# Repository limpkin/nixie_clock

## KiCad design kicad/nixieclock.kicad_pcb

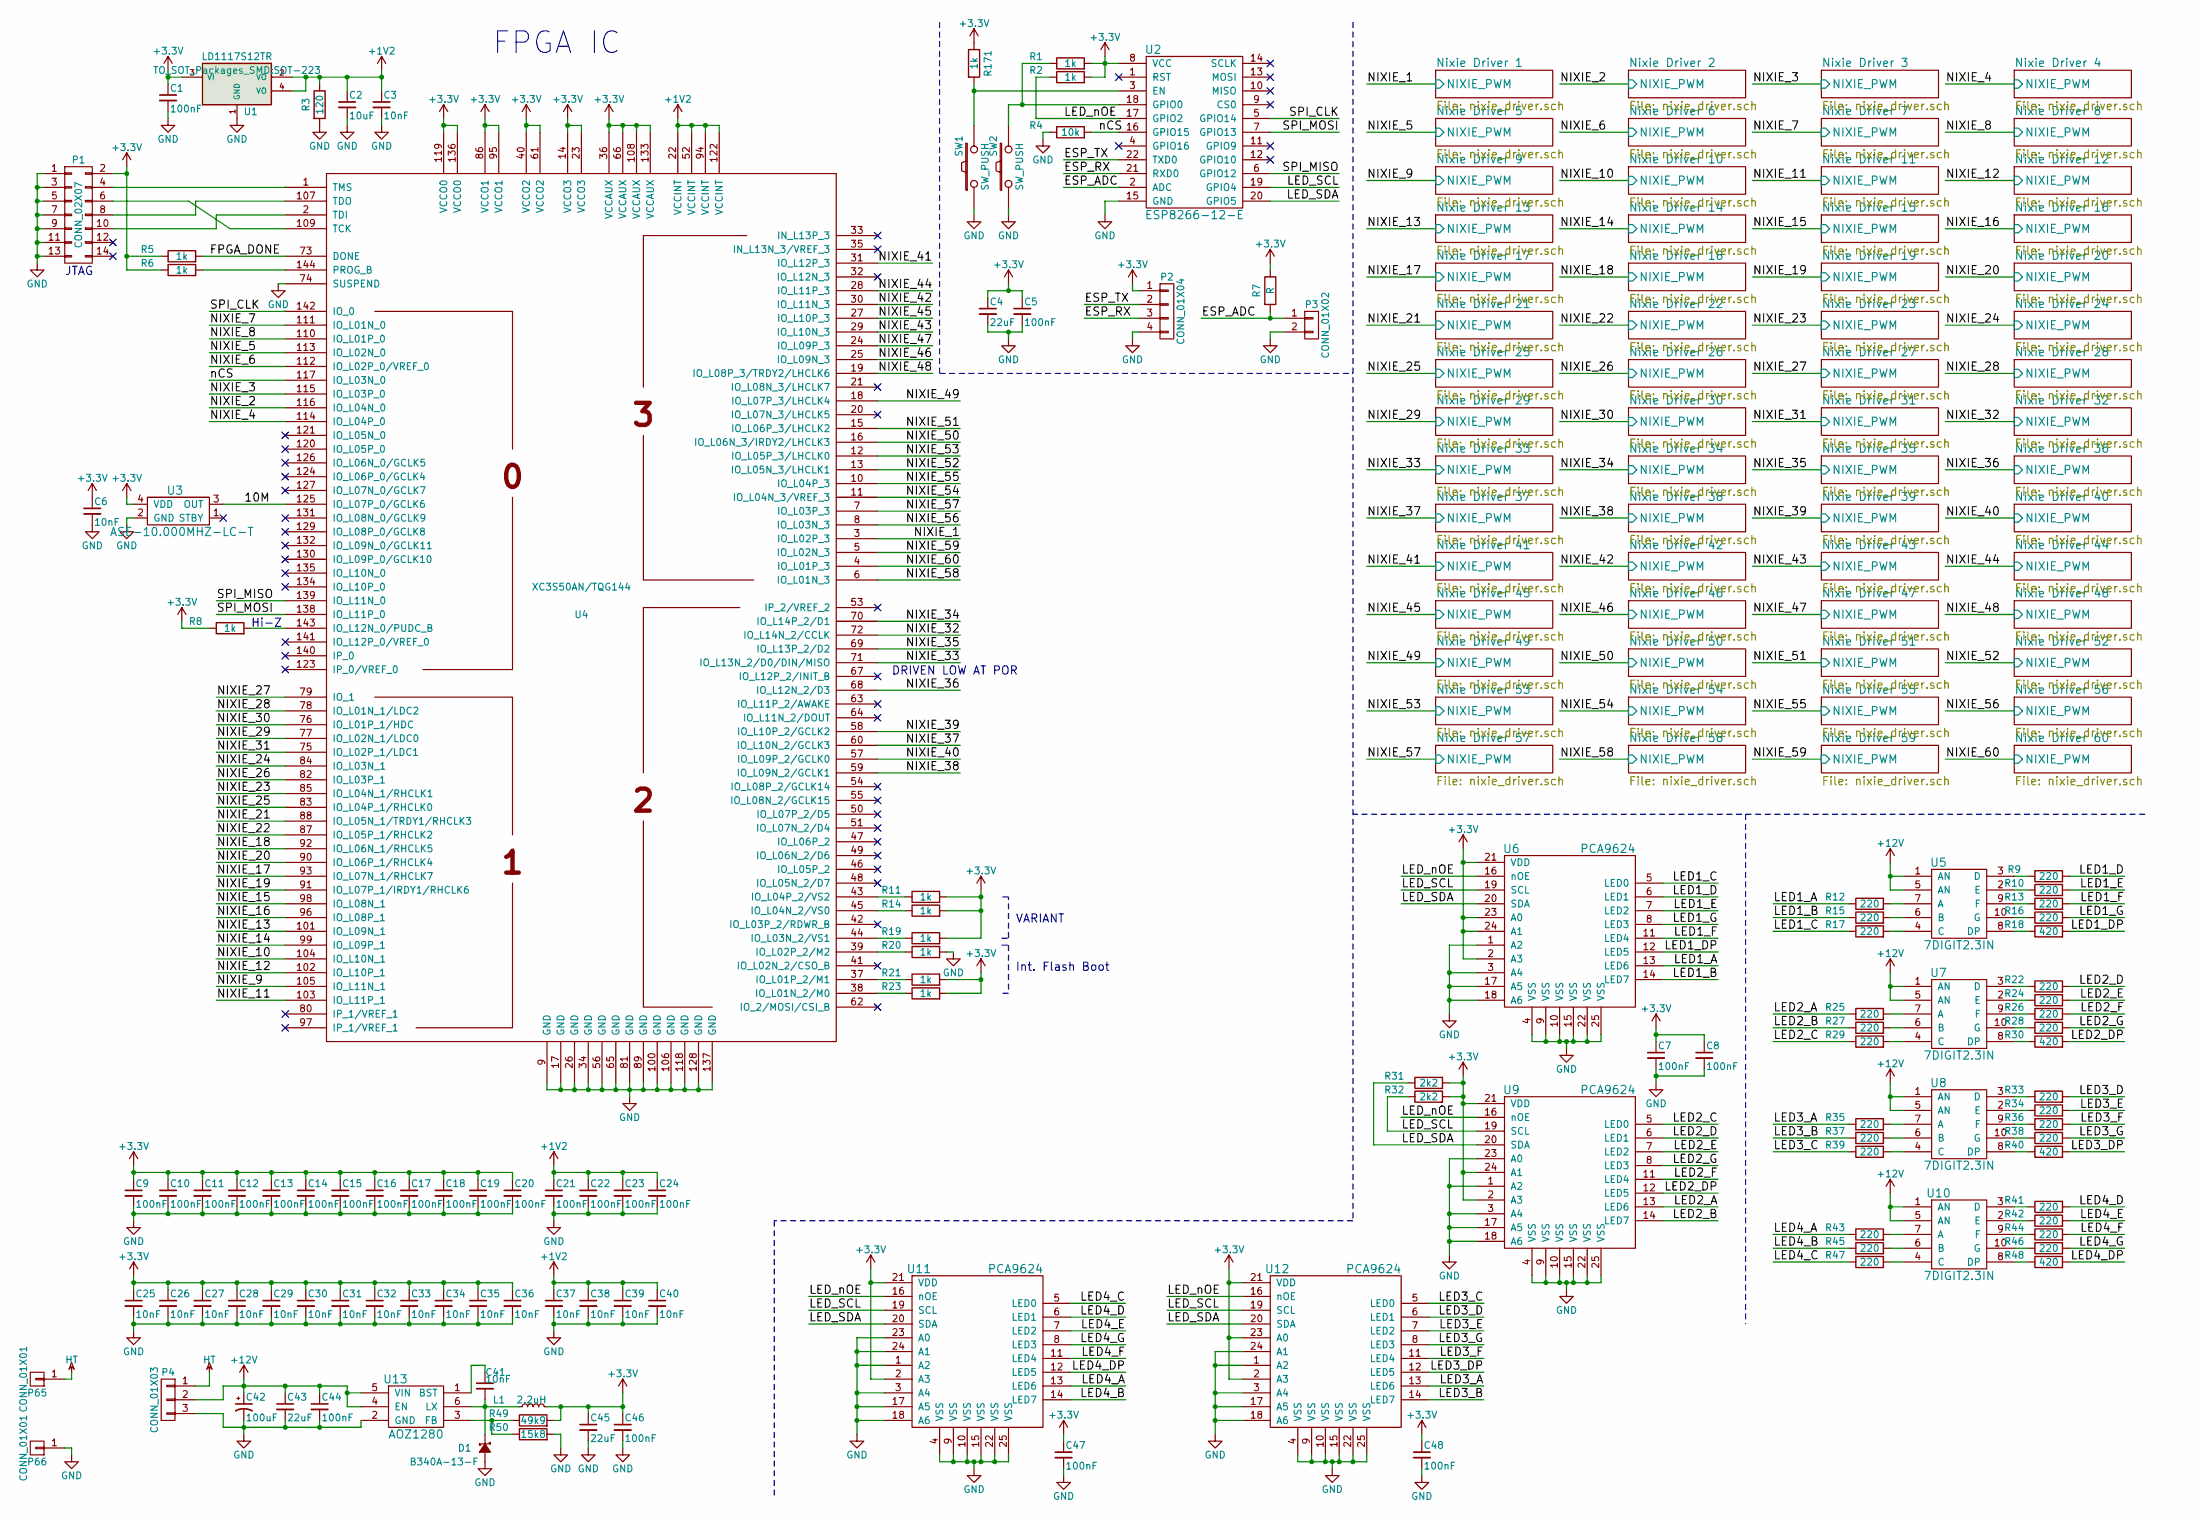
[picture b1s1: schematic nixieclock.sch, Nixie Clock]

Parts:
C1, C5, C7, C8, C9, C10, C11, C12, C13, C14, C15, C16, C17, C18, C19, C20, C21, C22, C23, C24, C44, C46, C47, C48: 100nF; C_0603_HandSoldering
C2: 10uF; C_0603_HandSoldering
C3, C6, C25, C26, C27, C28, C29, C30, C31, C32, C33, C34, C35, C36, C37, C38, C39, C40, C41: 10nF; C_0603_HandSoldering
C4, C43, C45: 22uF; C_0805_HandSoldering
C42: 100uF; C_Radial_D5_L11_P2.5
D1: B340A-13-F; DIODE_SMA
L1: 2.2uH; IND_6x6mm
P1: CONN_02X07; Pin_Header_Straight_2x07
P2: CONN_01X04; Pin_Header_Straight_1x04
P3: CONN_01X02; Pin_Header_Straight_1x02
P4: CONN_01X03; CON_SOLDER_POW_3
P65: CONN_01X01; RING_HV
P66: CONN_01X01; RING_GND
R1, R2, R5, R6, R8, R11, R14, R19, R20, R21, R23, R171: 1k; R_0603_HandSoldering
R3: 120; R_0603_HandSoldering
R4: 10k; R_0603_HandSoldering
R7: R; R_0603_HandSoldering
R9, R10, R12, R13, R15, R16, R17, R22, R24, R25, R26, R27, R28, R29, R33, R34, R35, R36, R37, R38, R39, R41, R42, R43, R44, R45, R46, R47: 220; R_0603_HandSoldering
R18, R30, R40, R48: 420; R_0603_HandSoldering
R31, R32: 2k2; R_0603_HandSoldering
R49: 49k9; R_0603_HandSoldering
R50: 15k8; R_0603_HandSoldering
SW1, SW2: SW_PUSH; BUT_FSM4JSMATR
U1: LD1117S12TR; SOT-223
U2: ESP8266-12-E; ESP12E
U3: ASE-10.000MHZ-LC-T; XTAL_3.2_2.5
U4: XC3S50AN/TQG144; TQFP-144_20x20mm_Pitch0.5mm
U5, U7, U8, U10: 7DIGIT2.3IN
U6, U9, U11, U12: PCA9624; HVQFN24
U13: AOZ1280; SOT-23-6

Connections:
+1V2: C2.1, C3.1, C21.1, C22.1, C23.1, C24.1, C37.1, C38.1, C39.1, C40.1, R3.1, U1.2 (VO), U1.4 (VO), U4.22 (VCCINT), U4.52 (VCCINT), U4.94 (VCCINT), U4.122 (VCCINT)
+3V3: C1.1, C4.1, C5.1, C6.1, C7.1, C8.1, C9.1, C10.1, C11.1, C12.1, C13.1, C14.1, C15.1, C16.1, C17.1, C18.1, C19.1, C20.1, C25.1, C26.1, C27.1, C28.1, C29.1, C30.1, C31.1, C32.1, C33.1, C34.1, C35.1, C36.1, C45.1, C46.1, C47.1, C48.1, L1.2, P1.2, P2.1, R1.2, R2.2, R5.1, R6.1, R7.1, R8.1, R11.2, R14.2, R19.2, R21.2, R23.2, R31.2, R32.2, R49.2, R171.1, U1.3 (VI), U2.8 (VCC), U3.4 (VDD), U4.14 (VCCO3), U4.23 (VCCO3), U4.36 (VCCAUX), U4.40 (VCCO2), U4.61 (VCCO2), U4.66 (VCCAUX), U4.86 (VCCO1), U4.95 (VCCO1), U4.108 (VCCAUX), U4.119 (VCCO0), U4.133 (VCCAUX), U4.136 (VCCO0), U6.2 (A3), U6.21 (VDD), U6.23 (A0), U6.24 (A1), U9.2 (A3), U9.21 (VDD), U9.24 (A1), U11.2 (A3), U11.21 (VDD), U12.2 (A3), U12.21 (VDD), U12.23 (A0)
+12V: C42.1, C43.1, C44.1, P4.2, U5.1 (AN), U5.5 (AN), U7.1 (AN), U7.5 (AN), U8.1 (AN), U8.5 (AN), U10.1 (AN), U10.5 (AN), U13.4 (EN), U13.5 (VIN)
/10M: U3.3 (OUT), U4.125 (IO_L07P_0/GCLK6)
/ESP_ADC: P3.1, R7.2, U2.2 (ADC)
/ESP_RX: P2.3, U2.21 (RXD0)
/ESP_TX: P2.2, U2.22 (TXD0)
/FPGA_DONE: R5.2, U4.73 (DONE)
/LED1_A: R12.1, U6.13 (LED6)
/LED1_B: R15.1, U6.14 (LED7)
/LED1_C: R17.1, U6.5 (LED0)
/LED1_D: R9.2, U6.6 (LED1)
/LED1_DP: R18.2, U6.12 (LED5)
/LED1_E: R10.2, U6.7 (LED2)
/LED1_F: R13.2, U6.11 (LED4)
/LED1_G: R16.2, U6.8 (LED3)
/LED2_A: R25.1, U9.13 (LED6)
/LED2_B: R27.1, U9.14 (LED7)
/LED2_C: R29.1, U9.5 (LED0)
/LED2_D: R22.2, U9.6 (LED1)
/LED2_DP: R30.2, U9.12 (LED5)
/LED2_E: R24.2, U9.7 (LED2)
/LED2_F: R26.2, U9.11 (LED4)
/LED2_G: R28.2, U9.8 (LED3)
/LED3_A: R35.1, U12.13 (LED6)
/LED3_B: R37.1, U12.14 (LED7)
/LED3_C: R39.1, U12.5 (LED0)
/LED3_D: R33.2, U12.6 (LED1)
/LED3_DP: R40.2, U12.12 (LED5)
/LED3_E: R34.2, U12.7 (LED2)
/LED3_F: R36.2, U12.11 (LED4)
/LED3_G: R38.2, U12.8 (LED3)
/LED4_A: R43.1, U11.13 (LED6)
/LED4_B: R45.1, U11.14 (LED7)
/LED4_C: R47.1, U11.5 (LED0)
/LED4_D: R41.2, U11.6 (LED1)
/LED4_DP: R48.2, U11.12 (LED5)
/LED4_E: R42.2, U11.7 (LED2)
/LED4_F: R44.2, U11.11 (LED4)
/LED4_G: R46.2, U11.8 (LED3)
/LED_SCL: R32.1, U2.19 (GPIO4), U6.19 (SCL), U9.19 (SCL), U11.19 (SCL), U12.19 (SCL)
/LED_SDA: R31.1, U2.20 (GPIO5), U6.20 (SDA), U9.20 (SDA), U11.20 (SDA), U12.20 (SDA)
/LED_nOE: R2.1, U2.17 (GPIO2), U6.16 (nOE), U9.16 (nOE), U11.16 (nOE), U12.16 (nOE)
/Nixie Driver 1/NIXIE_PWM: U4.3 (IO_L02P_3); also elsewhere on the board
/Nixie Driver 2/NIXIE_PWM: U4.116 (IO_L04N_0); also elsewhere on the board
/Nixie Driver 3/NIXIE_PWM: U4.115 (IO_L03P_0); also elsewhere on the board
/Nixie Driver 4/NIXIE_PWM: U4.114 (IO_L04P_0); also elsewhere on the board
/Nixie Driver 5/NIXIE_PWM: U4.113 (IO_L02N_0); also elsewhere on the board
/Nixie Driver 6/NIXIE_PWM: U4.112 (IO_L02P_0/VREF_0); also elsewhere on the board
/Nixie Driver 7/NIXIE_PWM: U4.111 (IO_L01N_0); also elsewhere on the board
/Nixie Driver 8/NIXIE_PWM: U4.110 (IO_L01P_0); also elsewhere on the board
/Nixie Driver 9/NIXIE_PWM: U4.105 (IO_L11N_1); also elsewhere on the board
/Nixie Driver 10/NIXIE_PWM: U4.104 (IO_L10N_1); also elsewhere on the board
/Nixie Driver 11/NIXIE_PWM: U4.103 (IO_L11P_1); also elsewhere on the board
/Nixie Driver 12/NIXIE_PWM: U4.102 (IO_L10P_1); also elsewhere on the board
/Nixie Driver 13/NIXIE_PWM: U4.101 (IO_L09N_1); also elsewhere on the board
/Nixie Driver 14/NIXIE_PWM: U4.99 (IO_L09P_1); also elsewhere on the board
/Nixie Driver 15/NIXIE_PWM: U4.98 (IO_L08N_1); also elsewhere on the board
/Nixie Driver 16/NIXIE_PWM: U4.96 (IO_L08P_1); also elsewhere on the board
/Nixie Driver 17/NIXIE_PWM: U4.93 (IO_L07N_1/RHCLK7); also elsewhere on the board
/Nixie Driver 18/NIXIE_PWM: U4.92 (IO_L06N_1/RHCLK5); also elsewhere on the board
/Nixie Driver 19/NIXIE_PWM: U4.91 (IO_L07P_1/IRDY1/RHCLK6); also elsewhere on the board
/Nixie Driver 20/NIXIE_PWM: U4.90 (IO_L06P_1/RHCLK4); also elsewhere on the board
/Nixie Driver 21/NIXIE_PWM: U4.88 (IO_L05N_1/TRDY1/RHCLK3); also elsewhere on the board
/Nixie Driver 22/NIXIE_PWM: U4.87 (IO_L05P_1/RHCLK2); also elsewhere on the board
/Nixie Driver 23/NIXIE_PWM: U4.85 (IO_L04N_1/RHCLK1); also elsewhere on the board
/Nixie Driver 24/NIXIE_PWM: U4.84 (IO_L03N_1); also elsewhere on the board
/Nixie Driver 25/NIXIE_PWM: U4.83 (IO_L04P_1/RHCLK0); also elsewhere on the board
/Nixie Driver 26/NIXIE_PWM: U4.82 (IO_L03P_1); also elsewhere on the board
/Nixie Driver 27/NIXIE_PWM: U4.79 (IO_1); also elsewhere on the board
/Nixie Driver 28/NIXIE_PWM: U4.78 (IO_L01N_1/LDC2); also elsewhere on the board
/Nixie Driver 29/NIXIE_PWM: U4.77 (IO_L02N_1/LDC0); also elsewhere on the board
/Nixie Driver 30/NIXIE_PWM: U4.76 (IO_L01P_1/HDC); also elsewhere on the board
/Nixie Driver 31/NIXIE_PWM: U4.75 (IO_L02P_1/LDC1); also elsewhere on the board
/Nixie Driver 32/NIXIE_PWM: U4.72 (IO_L14N_2/CCLK); also elsewhere on the board
/Nixie Driver 33/NIXIE_PWM: U4.71 (IO_L13N_2/D0/DIN/MISO); also elsewhere on the board
/Nixie Driver 34/NIXIE_PWM: U4.70 (IO_L14P_2/D1); also elsewhere on the board
/Nixie Driver 35/NIXIE_PWM: U4.69 (IO_L13P_2/D2); also elsewhere on the board
/Nixie Driver 36/NIXIE_PWM: U4.68 (IO_L12N_2/D3); also elsewhere on the board
/Nixie Driver 37/NIXIE_PWM: U4.60 (IO_L10N_2/GCLK3); also elsewhere on the board
/Nixie Driver 38/NIXIE_PWM: U4.59 (IO_L09N_2/GCLK1); also elsewhere on the board
/Nixie Driver 39/NIXIE_PWM: U4.58 (IO_L10P_2/GCLK2); also elsewhere on the board
/Nixie Driver 40/NIXIE_PWM: U4.57 (IO_L09P_2/GCLK0); also elsewhere on the board
/Nixie Driver 41/NIXIE_PWM: U4.31 (IO_L12P_3); also elsewhere on the board
/Nixie Driver 42/NIXIE_PWM: U4.30 (IO_L11N_3); also elsewhere on the board
/Nixie Driver 43/NIXIE_PWM: U4.29 (IO_L10N_3); also elsewhere on the board
/Nixie Driver 44/NIXIE_PWM: U4.28 (IO_L11P_3); also elsewhere on the board
/Nixie Driver 45/NIXIE_PWM: U4.27 (IO_L10P_3); also elsewhere on the board
/Nixie Driver 46/NIXIE_PWM: U4.25 (IO_L09N_3); also elsewhere on the board
/Nixie Driver 47/NIXIE_PWM: U4.24 (IO_L09P_3); also elsewhere on the board
/Nixie Driver 48/NIXIE_PWM: U4.19 (IO_L08P_3/TRDY2/LHCLK6); also elsewhere on the board
/Nixie Driver 49/NIXIE_PWM: U4.18 (IO_L07P_3/LHCLK4); also elsewhere on the board
/Nixie Driver 50/NIXIE_PWM: U4.16 (IO_L06N_3/IRDY2/LHCLK3); also elsewhere on the board
/Nixie Driver 51/NIXIE_PWM: U4.15 (IO_L06P_3/LHCLK2); also elsewhere on the board
/Nixie Driver 52/NIXIE_PWM: U4.13 (IO_L05N_3/LHCLK1); also elsewhere on the board
/Nixie Driver 53/NIXIE_PWM: U4.12 (IO_L05P_3/LHCLK0); also elsewhere on the board
/Nixie Driver 54/NIXIE_PWM: U4.11 (IO_L04N_3/VREF_3); also elsewhere on the board
/Nixie Driver 55/NIXIE_PWM: U4.10 (IO_L04P_3); also elsewhere on the board
/Nixie Driver 56/NIXIE_PWM: U4.8 (IO_L03N_3); also elsewhere on the board
/Nixie Driver 57/NIXIE_PWM: U4.7 (IO_L03P_3); also elsewhere on the board
/Nixie Driver 58/NIXIE_PWM: U4.6 (IO_L01N_3); also elsewhere on the board
/Nixie Driver 59/NIXIE_PWM: U4.5 (IO_L02N_3); also elsewhere on the board
/Nixie Driver 60/NIXIE_PWM: U4.4 (IO_L01P_3); also elsewhere on the board
/SPI_CLK: U2.5 (GPIO14), U4.142 (IO_0)
/SPI_MISO: U2.6 (GPIO12), U4.139 (IO_L11N_0)
/SPI_MOSI: U2.7 (GPIO13), U4.138 (IO_L11P_0)
/nCS: R4.2, U2.16 (GPIO15), U4.117 (IO_L03N_0)
GND: C1.2, C2.2, C3.2, C4.2, C5.2, C6.2, C7.2, C8.2, C9.2, C10.2, C11.2, C12.2, C13.2, C14.2, C15.2, C16.2, C17.2, C18.2, C19.2, C20.2, C21.2, C22.2, C23.2, C24.2, C25.2, C26.2, C27.2, C28.2, C29.2, C30.2, C31.2, C32.2, C33.2, C34.2, C35.2, C36.2, C37.2, C38.2, C39.2, C40.2, C42.2, C43.2, C44.2, C45.2, C46.2, C47.2, C48.2, D1.2 (A), P1.1, P1.3, P1.5, P1.7, P1.9, P1.11, P1.13, P2.4, P3.2, P4.3, P66.1, R3.2, R4.1, R20.2, R50.2, SW1.1, SW2.1, U1.1 (GND), U2.15 (GND), U3.2 (GND), U4.9 (GND), U4.17 (GND), U4.26 (GND), U4.34 (GND), U4.56 (GND), U4.65 (GND), U4.74 (SUSPEND), U4.81 (GND), U4.89 (GND), U4.100 (GND), U4.106 (GND), U4.118 (GND), U4.128 (GND), U4.137 (GND), U6.1 (A2), U6.3 (A4), U6.4 (VSS), U6.9 (VSS), U6.10 (VSS), U6.15 (VSS), U6.17 (A5), U6.18 (A6), U6.22 (VSS), U6.25 (VSS), U9.1 (A2), U9.3 (A4), U9.4 (VSS), U9.9 (VSS), U9.10 (VSS), U9.15 (VSS), U9.17 (A5), U9.18 (A6), U9.22 (VSS), U9.23 (A0), U9.25 (VSS), U11.1 (A2), U11.3 (A4), U11.4 (VSS), U11.9 (VSS), U11.10 (VSS), U11.15 (VSS), U11.17 (A5), U11.18 (A6), U11.22 (VSS), U11.23 (A0), U11.24 (A1), U11.25 (VSS), U12.1 (A2), U12.3 (A4), U12.4 (VSS), U12.9 (VSS), U12.10 (VSS), U12.15 (VSS), U12.17 (A5), U12.18 (A6), U12.22 (VSS), U12.24 (A1), U12.25 (VSS), U13.2 (GND); also elsewhere on the board
HT: P4.1, P65.1; also elsewhere on the board
unnamed: C41.1, U13.1 (BST)
unnamed: C41.2, D1.1 (K), L1.1, U13.6 (LX)
unnamed: P1.4, U4.1 (TMS)
unnamed: P1.6, U4.109 (TCK)
unnamed: P1.8, U4.107 (TDO)
unnamed: P1.10, U4.2 (TDI)
unnamed: R1.1, SW2.2, U2.18 (GPIO0)
unnamed: R6.2, U4.144 (PROG_B)
unnamed: R8.2, U4.143 (IO_L12N_0/PUDC_B)
unnamed: R9.1, U5.3 (D)
unnamed: R10.1, U5.2 (E)
unnamed: R11.1, U4.43 (IO_L04P_2/VS2)
unnamed: R12.2, U5.7 (A)
unnamed: R13.1, U5.9 (F)
unnamed: R14.1, U4.45 (IO_L04N_2/VS0)
unnamed: R15.2, U5.6 (B)
unnamed: R16.1, U5.10 (G)
unnamed: R17.2, U5.4 (C)
unnamed: R18.1, U5.8 (DP)
unnamed: R19.1, U4.44 (IO_L03N_2/VS1)
unnamed: R20.1, U4.39 (IO_L02P_2/M2)
unnamed: R21.1, U4.37 (IO_L01P_2/M1)
unnamed: R22.1, U7.3 (D)
unnamed: R23.1, U4.38 (IO_L01N_2/M0)
unnamed: R24.1, U7.2 (E)
unnamed: R25.2, U7.7 (A)
unnamed: R26.1, U7.9 (F)
unnamed: R27.2, U7.6 (B)
unnamed: R28.1, U7.10 (G)
unnamed: R29.2, U7.4 (C)
unnamed: R30.1, U7.8 (DP)
unnamed: R33.1, U8.3 (D)
unnamed: R34.1, U8.2 (E)
unnamed: R35.2, U8.7 (A)
unnamed: R36.1, U8.9 (F)
unnamed: R37.2, U8.6 (B)
unnamed: R38.1, U8.10 (G)
unnamed: R39.2, U8.4 (C)
unnamed: R40.1, U8.8 (DP)
unnamed: R41.1, U10.3 (D)
unnamed: R42.1, U10.2 (E)
unnamed: R43.2, U10.7 (A)
unnamed: R44.1, U10.9 (F)
unnamed: R45.2, U10.6 (B)
unnamed: R46.1, U10.10 (G)
unnamed: R47.2, U10.4 (C)
unnamed: R48.1, U10.8 (DP)
unnamed: R49.1, R50.1, U13.3 (FB)
unnamed: R171.2, SW1.2, U2.3 (EN)

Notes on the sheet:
JTAG
Int. Flash Boot
Hi-Z
DRIVEN LOW AT POR
VARIANT
FPGA IC

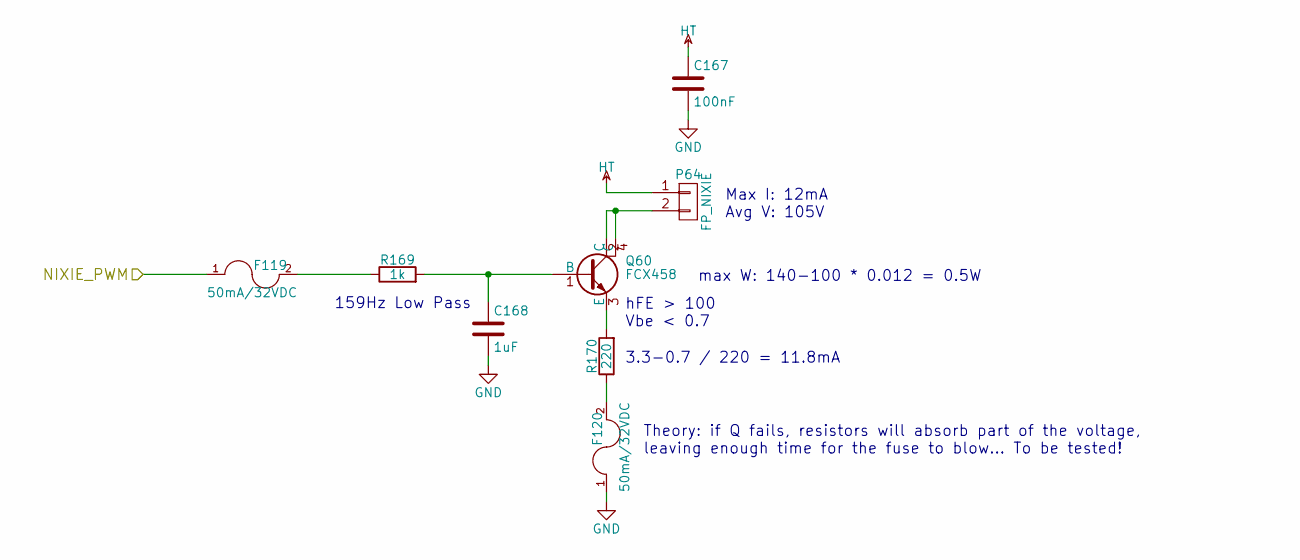
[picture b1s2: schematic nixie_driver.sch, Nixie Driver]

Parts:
C49: 100nF; C_0805_HandSoldering
C50: 1uF; C_0603_HandSoldering
F1, F2: 50mA/32VDC; C_0603_HandSoldering
P5: FP_NIXIE; NIXIE_TH
Q1: FCX458; SOT89-3_Housing_Handsoldering
R51: 1k; R_0603_HandSoldering
R52: 220; R_0603_HandSoldering

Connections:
/Nixie Driver 4/NIXIE_PWM: F1.1; also elsewhere on the board
GND: C49.2, C50.2, F2.1; also elsewhere on the board
HT: C49.1, P5.1; also elsewhere on the board
unnamed: C50.1, Q1.1 (B), R51.2
unnamed: F1.2, R51.1
unnamed: F2.2, R52.1
unnamed: P5.2, Q1.2 (C), Q1.4 (C)
unnamed: Q1.3 (E), R52.2

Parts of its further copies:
C51, C53, C55, C57, C59, C61, C63, C65, C67, C69, C71, C73, C75, C77, C79, C81, C83, C85, C87, C89, C91, C93, C95, C97, C99, C101, C103, C105, C107, C109, C111, C113, C115, C117, C119, C121, C123, C125, C127, C129, C131, C133, C135, C137, C139, C141, C143, C145, C147, C149, C151, C153, C155, C157, C159, C161, C163, C165, C167: 100nF; C_0805_HandSoldering
C52, C54, C56, C58, C60, C62, C64, C66, C68, C70, C72, C74, C76, C78, C80, C82, C84, C86, C88, C90, C92, C94, C96, C98, C100, C102, C104, C106, C108, C110, C112, C114, C116, C118, C120, C122, C124, C126, C128, C130, C132, C134, C136, C138, C140, C142, C144, C146, C148, C150, C152, C154, C156, C158, C160, C162, C164, C166, C168: 1uF; C_0603_HandSoldering
F3, F4, F5, F6, F7, F8, F9, F10, F11, F12, F13, F14, F15, F16, F17, F18, F19, F20, F21, F22, F23, F24, F25, F26, F27, F28, F29, F30, F31, F32, F33, F34, F35, F36, F37, F38, F39, F40, F41, F42, F43, F44, F45, F46, F47, F48, F49, F50, F51, F52, F53, F54, F55, F56, F57, F58, F59, F60, F61, F62, F63, F64, F65, F66, F67, F68, F69, F70, F71, F72, F73, F74, F75, F76, F77, F78, F79, F80, F81, F82, F83, F84, F85, F86, F87, F88, F89, F90, F91, F92, F93, F94, F95, F96, F97, F98, F99, F100, F101, F102, F103, F104, F105, F106, F107, F108, F109, F110, F111, F112, F113, F114, F115, F116, F117, F118, F119, F120: 50mA/32VDC; C_0603_HandSoldering
P6, P7, P8, P9, P10, P11, P12, P13, P14, P15, P16, P17, P18, P19, P20, P21, P22, P23, P24, P25, P26, P27, P28, P29, P30, P31, P32, P33, P34, P35, P36, P37, P38, P39, P40, P41, P42, P43, P44, P45, P46, P47, P48, P49, P50, P51, P52, P53, P54, P55, P56, P57, P58, P59, P60, P61, P62, P63, P64: FP_NIXIE; NIXIE_TH
Q2, Q3, Q4, Q5, Q6, Q7, Q8, Q9, Q10, Q11, Q12, Q13, Q14, Q15, Q16, Q17, Q18, Q19, Q20, Q21, Q22, Q23, Q24, Q25, Q26, Q27, Q28, Q29, Q30, Q31, Q32, Q33, Q34, Q35, Q36, Q37, Q38, Q39, Q40, Q41, Q42, Q43, Q44, Q45, Q46, Q47, Q48, Q49, Q50, Q51, Q52, Q53, Q54, Q55, Q56, Q57, Q58, Q59, Q60: FCX458; SOT89-3_Housing_Handsoldering
R53, R55, R57, R59, R61, R63, R65, R67, R69, R71, R73, R75, R77, R79, R81, R83, R85, R87, R89, R91, R93, R95, R97, R99, R101, R103, R105, R107, R109, R111, R113, R115, R117, R119, R121, R123, R125, R127, R129, R131, R133, R135, R137, R139, R141, R143, R145, R147, R149, R151, R153, R155, R157, R159, R161, R163, R165, R167, R169: 1k; R_0603_HandSoldering
R54, R56, R58, R60, R62, R64, R66, R68, R70, R72, R74, R76, R78, R80, R82, R84, R86, R88, R90, R92, R94, R96, R98, R100, R102, R104, R106, R108, R110, R112, R114, R116, R118, R120, R122, R124, R126, R128, R130, R132, R134, R136, R138, R140, R142, R144, R146, R148, R150, R152, R154, R156, R158, R160, R162, R164, R166, R168, R170: 220; R_0603_HandSoldering

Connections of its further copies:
/Nixie Driver 1/NIXIE_PWM: F89.1; also elsewhere on the board
/Nixie Driver 2/NIXIE_PWM: F59.1; also elsewhere on the board
/Nixie Driver 3/NIXIE_PWM: F29.1; also elsewhere on the board
/Nixie Driver 5/NIXIE_PWM: F91.1; also elsewhere on the board
/Nixie Driver 6/NIXIE_PWM: F61.1; also elsewhere on the board
/Nixie Driver 7/NIXIE_PWM: F31.1; also elsewhere on the board
/Nixie Driver 8/NIXIE_PWM: F3.1; also elsewhere on the board
/Nixie Driver 9/NIXIE_PWM: F93.1; also elsewhere on the board
/Nixie Driver 10/NIXIE_PWM: F63.1; also elsewhere on the board
/Nixie Driver 11/NIXIE_PWM: F33.1; also elsewhere on the board
/Nixie Driver 12/NIXIE_PWM: F5.1; also elsewhere on the board
/Nixie Driver 13/NIXIE_PWM: F95.1; also elsewhere on the board
/Nixie Driver 14/NIXIE_PWM: F65.1; also elsewhere on the board
/Nixie Driver 15/NIXIE_PWM: F35.1; also elsewhere on the board
/Nixie Driver 16/NIXIE_PWM: F7.1; also elsewhere on the board
/Nixie Driver 17/NIXIE_PWM: F97.1; also elsewhere on the board
/Nixie Driver 18/NIXIE_PWM: F67.1; also elsewhere on the board
/Nixie Driver 19/NIXIE_PWM: F37.1; also elsewhere on the board
/Nixie Driver 20/NIXIE_PWM: F9.1; also elsewhere on the board
/Nixie Driver 21/NIXIE_PWM: F99.1; also elsewhere on the board
/Nixie Driver 22/NIXIE_PWM: F69.1; also elsewhere on the board
/Nixie Driver 23/NIXIE_PWM: F39.1; also elsewhere on the board
/Nixie Driver 24/NIXIE_PWM: F11.1; also elsewhere on the board
/Nixie Driver 25/NIXIE_PWM: F101.1; also elsewhere on the board
/Nixie Driver 26/NIXIE_PWM: F71.1; also elsewhere on the board
/Nixie Driver 27/NIXIE_PWM: F41.1; also elsewhere on the board
/Nixie Driver 28/NIXIE_PWM: F13.1; also elsewhere on the board
/Nixie Driver 29/NIXIE_PWM: F103.1; also elsewhere on the board
/Nixie Driver 30/NIXIE_PWM: F73.1; also elsewhere on the board
/Nixie Driver 31/NIXIE_PWM: F43.1; also elsewhere on the board
/Nixie Driver 32/NIXIE_PWM: F15.1; also elsewhere on the board
/Nixie Driver 33/NIXIE_PWM: F105.1; also elsewhere on the board
/Nixie Driver 34/NIXIE_PWM: F75.1; also elsewhere on the board
/Nixie Driver 35/NIXIE_PWM: F45.1; also elsewhere on the board
/Nixie Driver 36/NIXIE_PWM: F17.1; also elsewhere on the board
/Nixie Driver 37/NIXIE_PWM: F107.1; also elsewhere on the board
/Nixie Driver 38/NIXIE_PWM: F77.1; also elsewhere on the board
/Nixie Driver 39/NIXIE_PWM: F47.1; also elsewhere on the board
/Nixie Driver 40/NIXIE_PWM: F19.1; also elsewhere on the board
/Nixie Driver 41/NIXIE_PWM: F109.1; also elsewhere on the board
/Nixie Driver 42/NIXIE_PWM: F79.1; also elsewhere on the board
/Nixie Driver 43/NIXIE_PWM: F49.1; also elsewhere on the board
/Nixie Driver 44/NIXIE_PWM: F21.1; also elsewhere on the board
/Nixie Driver 45/NIXIE_PWM: F111.1; also elsewhere on the board
/Nixie Driver 46/NIXIE_PWM: F81.1; also elsewhere on the board
/Nixie Driver 47/NIXIE_PWM: F51.1; also elsewhere on the board
/Nixie Driver 48/NIXIE_PWM: F23.1; also elsewhere on the board
/Nixie Driver 49/NIXIE_PWM: F113.1; also elsewhere on the board
/Nixie Driver 50/NIXIE_PWM: F83.1; also elsewhere on the board
/Nixie Driver 51/NIXIE_PWM: F53.1; also elsewhere on the board
/Nixie Driver 52/NIXIE_PWM: F25.1; also elsewhere on the board
/Nixie Driver 53/NIXIE_PWM: F115.1; also elsewhere on the board
/Nixie Driver 54/NIXIE_PWM: F85.1; also elsewhere on the board
/Nixie Driver 55/NIXIE_PWM: F55.1; also elsewhere on the board
/Nixie Driver 56/NIXIE_PWM: F27.1; also elsewhere on the board
/Nixie Driver 57/NIXIE_PWM: F117.1; also elsewhere on the board
/Nixie Driver 58/NIXIE_PWM: F87.1; also elsewhere on the board
/Nixie Driver 59/NIXIE_PWM: F57.1; also elsewhere on the board
/Nixie Driver 60/NIXIE_PWM: F119.1; also elsewhere on the board
GND: C51.2, C52.2, C53.2, C54.2, C55.2, C56.2, C57.2, C58.2, C59.2, C60.2, C61.2, C62.2, C63.2, C64.2, C65.2, C66.2, C67.2, C68.2, C69.2, C70.2, C71.2, C72.2, C73.2, C74.2, C75.2, C76.2, C77.2, C78.2, C79.2, C80.2, C81.2, C82.2, C83.2, C84.2, C85.2, C86.2, C87.2, C88.2, C89.2, C90.2, C91.2, C92.2, C93.2, C94.2, C95.2, C96.2, C97.2, C98.2, C99.2, C100.2, C101.2, C102.2, C103.2, C104.2, C105.2, C106.2, C107.2, C108.2, C109.2, C110.2, C111.2, C112.2, C113.2, C114.2, C115.2, C116.2, C117.2, C118.2, C119.2, C120.2, C121.2, C122.2, C123.2, C124.2, C125.2, C126.2, C127.2, C128.2, C129.2, C130.2, C131.2, C132.2, C133.2, C134.2, C135.2, C136.2, C137.2, C138.2, C139.2, C140.2, C141.2, C142.2, C143.2, C144.2, C145.2, C146.2, C147.2, C148.2, C149.2, C150.2, C151.2, C152.2, C153.2, C154.2, C155.2, C156.2, C157.2, C158.2, C159.2, C160.2, C161.2, C162.2, C163.2, C164.2, C165.2, C166.2, C167.2, C168.2, F4.1, F6.1, F8.1, F10.1, F12.1, F14.1, F16.1, F18.1, F20.1, F22.1, F24.1, F26.1, F28.1, F30.1, F32.1, F34.1, F36.1, F38.1, F40.1, F42.1, F44.1, F46.1, F48.1, F50.1, F52.1, F54.1, F56.1, F58.1, F60.1, F62.1, F64.1, F66.1, F68.1, F70.1, F72.1, F74.1, F76.1, F78.1, F80.1, F82.1, F84.1, F86.1, F88.1, F90.1, F92.1, F94.1, F96.1, F98.1, F100.1, F102.1, F104.1, F106.1, F108.1, F110.1, F112.1, F114.1, F116.1, F118.1, F120.1; also elsewhere on the board
HT: C51.1, C53.1, C55.1, C57.1, C59.1, C61.1, C63.1, C65.1, C67.1, C69.1, C71.1, C73.1, C75.1, C77.1, C79.1, C81.1, C83.1, C85.1, C87.1, C89.1, C91.1, C93.1, C95.1, C97.1, C99.1, C101.1, C103.1, C105.1, C107.1, C109.1, C111.1, C113.1, C115.1, C117.1, C119.1, C121.1, C123.1, C125.1, C127.1, C129.1, C131.1, C133.1, C135.1, C137.1, C139.1, C141.1, C143.1, C145.1, C147.1, C149.1, C151.1, C153.1, C155.1, C157.1, C159.1, C161.1, C163.1, C165.1, C167.1, P6.1, P7.1, P8.1, P9.1, P10.1, P11.1, P12.1, P13.1, P14.1, P15.1, P16.1, P17.1, P18.1, P19.1, P20.1, P21.1, P22.1, P23.1, P24.1, P25.1, P26.1, P27.1, P28.1, P29.1, P30.1, P31.1, P32.1, P33.1, P34.1, P35.1, P36.1, P37.1, P38.1, P39.1, P40.1, P41.1, P42.1, P43.1, P44.1, P45.1, P46.1, P47.1, P48.1, P49.1, P50.1, P51.1, P52.1, P53.1, P54.1, P55.1, P56.1, P57.1, P58.1, P59.1, P60.1, P61.1, P62.1, P63.1, P64.1; also elsewhere on the board
unnamed: C52.1, Q2.1 (B), R53.2
unnamed: C54.1, Q3.1 (B), R55.2
unnamed: C56.1, Q4.1 (B), R57.2
unnamed: C58.1, Q5.1 (B), R59.2
unnamed: C60.1, Q6.1 (B), R61.2
unnamed: C62.1, Q7.1 (B), R63.2
unnamed: C64.1, Q8.1 (B), R65.2
unnamed: C66.1, Q9.1 (B), R67.2
unnamed: C68.1, Q10.1 (B), R69.2
unnamed: C70.1, Q11.1 (B), R71.2
unnamed: C72.1, Q12.1 (B), R73.2
unnamed: C74.1, Q13.1 (B), R75.2
unnamed: C76.1, Q14.1 (B), R77.2
unnamed: C78.1, Q15.1 (B), R79.2
unnamed: C80.1, Q16.1 (B), R81.2
unnamed: C82.1, Q17.1 (B), R83.2
unnamed: C84.1, Q18.1 (B), R85.2
unnamed: C86.1, Q19.1 (B), R87.2
unnamed: C88.1, Q20.1 (B), R89.2
unnamed: C90.1, Q21.1 (B), R91.2
unnamed: C92.1, Q22.1 (B), R93.2
unnamed: C94.1, Q23.1 (B), R95.2
unnamed: C96.1, Q24.1 (B), R97.2
unnamed: C98.1, Q25.1 (B), R99.2
unnamed: C100.1, Q26.1 (B), R101.2
unnamed: C102.1, Q27.1 (B), R103.2
unnamed: C104.1, Q28.1 (B), R105.2
unnamed: C106.1, Q29.1 (B), R107.2
unnamed: C108.1, Q30.1 (B), R109.2
unnamed: C110.1, Q31.1 (B), R111.2
unnamed: C112.1, Q32.1 (B), R113.2
unnamed: C114.1, Q33.1 (B), R115.2
unnamed: C116.1, Q34.1 (B), R117.2
unnamed: C118.1, Q35.1 (B), R119.2
unnamed: C120.1, Q36.1 (B), R121.2
unnamed: C122.1, Q37.1 (B), R123.2
unnamed: C124.1, Q38.1 (B), R125.2
unnamed: C126.1, Q39.1 (B), R127.2
unnamed: C128.1, Q40.1 (B), R129.2
unnamed: C130.1, Q41.1 (B), R131.2
unnamed: C132.1, Q42.1 (B), R133.2
unnamed: C134.1, Q43.1 (B), R135.2
unnamed: C136.1, Q44.1 (B), R137.2
unnamed: C138.1, Q45.1 (B), R139.2
unnamed: C140.1, Q46.1 (B), R141.2
unnamed: C142.1, Q47.1 (B), R143.2
unnamed: C144.1, Q48.1 (B), R145.2
unnamed: C146.1, Q49.1 (B), R147.2
unnamed: C148.1, Q50.1 (B), R149.2
unnamed: C150.1, Q51.1 (B), R151.2
unnamed: C152.1, Q52.1 (B), R153.2
unnamed: C154.1, Q53.1 (B), R155.2
unnamed: C156.1, Q54.1 (B), R157.2
unnamed: C158.1, Q55.1 (B), R159.2
unnamed: C160.1, Q56.1 (B), R161.2
unnamed: C162.1, Q57.1 (B), R163.2
unnamed: C164.1, Q58.1 (B), R165.2
unnamed: C166.1, Q59.1 (B), R167.2
unnamed: C168.1, Q60.1 (B), R169.2
unnamed: F3.2, R53.1
unnamed: F4.2, R54.1
unnamed: F5.2, R55.1
unnamed: F6.2, R56.1
unnamed: F7.2, R57.1
unnamed: F8.2, R58.1
unnamed: F9.2, R59.1
unnamed: F10.2, R60.1
unnamed: F11.2, R61.1
unnamed: F12.2, R62.1
unnamed: F13.2, R63.1
unnamed: F14.2, R64.1
unnamed: F15.2, R65.1
unnamed: F16.2, R66.1
unnamed: F17.2, R67.1
unnamed: F18.2, R68.1
unnamed: F19.2, R69.1
unnamed: F20.2, R70.1
unnamed: F21.2, R71.1
unnamed: F22.2, R72.1
unnamed: F23.2, R73.1
unnamed: F24.2, R74.1
unnamed: F25.2, R75.1
unnamed: F26.2, R76.1
unnamed: F27.2, R77.1
unnamed: F28.2, R78.1
unnamed: F29.2, R79.1
unnamed: F30.2, R80.1
unnamed: F31.2, R81.1
unnamed: F32.2, R82.1
unnamed: F33.2, R83.1
unnamed: F34.2, R84.1
unnamed: F35.2, R85.1
unnamed: F36.2, R86.1
unnamed: F37.2, R87.1
unnamed: F38.2, R88.1
unnamed: F39.2, R89.1
unnamed: F40.2, R90.1
unnamed: F41.2, R91.1
unnamed: F42.2, R92.1
unnamed: F43.2, R93.1
unnamed: F44.2, R94.1
unnamed: F45.2, R95.1
unnamed: F46.2, R96.1
unnamed: F47.2, R97.1
unnamed: F48.2, R98.1
unnamed: F49.2, R99.1
unnamed: F50.2, R100.1
unnamed: F51.2, R101.1
unnamed: F52.2, R102.1
unnamed: F53.2, R103.1
unnamed: F54.2, R104.1
unnamed: F55.2, R105.1
unnamed: F56.2, R106.1
unnamed: F57.2, R107.1
unnamed: F58.2, R108.1
unnamed: F59.2, R109.1
unnamed: F60.2, R110.1
unnamed: F61.2, R111.1
unnamed: F62.2, R112.1
unnamed: F63.2, R113.1
unnamed: F64.2, R114.1
unnamed: F65.2, R115.1
unnamed: F66.2, R116.1
unnamed: F67.2, R117.1
unnamed: F68.2, R118.1
unnamed: F69.2, R119.1
unnamed: F70.2, R120.1
unnamed: F71.2, R121.1
unnamed: F72.2, R122.1
unnamed: F73.2, R123.1
unnamed: F74.2, R124.1
unnamed: F75.2, R125.1
unnamed: F76.2, R126.1
unnamed: F77.2, R127.1
unnamed: F78.2, R128.1
unnamed: F79.2, R129.1
unnamed: F80.2, R130.1
unnamed: F81.2, R131.1
unnamed: F82.2, R132.1
unnamed: F83.2, R133.1
unnamed: F84.2, R134.1
unnamed: F85.2, R135.1
unnamed: F86.2, R136.1
unnamed: F87.2, R137.1
unnamed: F88.2, R138.1
unnamed: F89.2, R139.1
unnamed: F90.2, R140.1
unnamed: F91.2, R141.1
unnamed: F92.2, R142.1
unnamed: F93.2, R143.1
unnamed: F94.2, R144.1
unnamed: F95.2, R145.1
unnamed: F96.2, R146.1
unnamed: F97.2, R147.1
unnamed: F98.2, R148.1
unnamed: F99.2, R149.1
unnamed: F100.2, R150.1
unnamed: F101.2, R151.1
unnamed: F102.2, R152.1
unnamed: F103.2, R153.1
unnamed: F104.2, R154.1
unnamed: F105.2, R155.1
unnamed: F106.2, R156.1
unnamed: F107.2, R157.1
unnamed: F108.2, R158.1
unnamed: F109.2, R159.1
unnamed: F110.2, R160.1
unnamed: F111.2, R161.1
unnamed: F112.2, R162.1
unnamed: F113.2, R163.1
unnamed: F114.2, R164.1
unnamed: F115.2, R165.1
unnamed: F116.2, R166.1
unnamed: F117.2, R167.1
unnamed: F118.2, R168.1
unnamed: F119.2, R169.1
unnamed: F120.2, R170.1
unnamed: P6.2, Q2.2 (C)
unnamed: P7.2, Q3.2 (C)
unnamed: P8.2, Q4.2 (C)
unnamed: P9.2, Q5.2 (C)
unnamed: P10.2, Q6.2 (C)
unnamed: P11.2, Q7.2 (C)
unnamed: P12.2, Q8.2 (C)
unnamed: P13.2, Q9.2 (C)
unnamed: P14.2, Q10.2 (C)
unnamed: P15.2, Q11.2 (C)
unnamed: P16.2, Q12.2 (C)
unnamed: P17.2, Q13.2 (C)
unnamed: P18.2, Q14.2 (C)
unnamed: P19.2, Q15.2 (C)
unnamed: P20.2, Q16.2 (C)
unnamed: P21.2, Q17.2 (C)
unnamed: P22.2, Q18.2 (C)
unnamed: P23.2, Q19.2 (C)
unnamed: P24.2, Q20.2 (C)
unnamed: P25.2, Q21.2 (C)
unnamed: P26.2, Q22.2 (C)
unnamed: P27.2, Q23.2 (C)
unnamed: P28.2, Q24.2 (C)
unnamed: P29.2, Q25.2 (C)
unnamed: P30.2, Q26.2 (C)
unnamed: P31.2, Q27.2 (C)
unnamed: P32.2, Q28.2 (C)
unnamed: P33.2, Q29.2 (C)
unnamed: P34.2, Q30.2 (C)
unnamed: P35.2, Q31.2 (C)
unnamed: P36.2, Q32.2 (C)
unnamed: P37.2, Q33.2 (C)
unnamed: P38.2, Q34.2 (C)
unnamed: P39.2, Q35.2 (C)
unnamed: P40.2, Q36.2 (C)
unnamed: P41.2, Q37.2 (C)
unnamed: P42.2, Q38.2 (C)
unnamed: P43.2, Q39.2 (C)
unnamed: P44.2, Q40.2 (C)
unnamed: P45.2, Q41.2 (C)
unnamed: P46.2, Q42.2 (C)
unnamed: P47.2, Q43.2 (C)
unnamed: P48.2, Q44.2 (C)
unnamed: P49.2, Q45.2 (C)
unnamed: P50.2, Q46.2 (C)
unnamed: P51.2, Q47.2 (C)
unnamed: P52.2, Q48.2 (C)
unnamed: P53.2, Q49.2 (C)
unnamed: P54.2, Q50.2 (C)
unnamed: P55.2, Q51.2 (C)
unnamed: P56.2, Q52.2 (C)
unnamed: P57.2, Q53.2 (C)
unnamed: P58.2, Q54.2 (C)
unnamed: P59.2, Q55.2 (C)
unnamed: P60.2, Q56.2 (C)
unnamed: P61.2, Q57.2 (C)
unnamed: P62.2, Q58.2 (C)
unnamed: P63.2, Q59.2 (C)
unnamed: P64.2, Q60.2 (C)
unnamed: Q2.3 (E), R54.2
unnamed: Q3.3 (E), R56.2
unnamed: Q4.3 (E), R58.2
unnamed: Q5.3 (E), R60.2
unnamed: Q6.3 (E), R62.2
unnamed: Q7.3 (E), R64.2
unnamed: Q8.3 (E), R66.2
unnamed: Q9.3 (E), R68.2
unnamed: Q10.3 (E), R70.2
unnamed: Q11.3 (E), R72.2
unnamed: Q12.3 (E), R74.2
unnamed: Q13.3 (E), R76.2
unnamed: Q14.3 (E), R78.2
unnamed: Q15.3 (E), R80.2
unnamed: Q16.3 (E), R82.2
unnamed: Q17.3 (E), R84.2
unnamed: Q18.3 (E), R86.2
unnamed: Q19.3 (E), R88.2
unnamed: Q20.3 (E), R90.2
unnamed: Q21.3 (E), R92.2
unnamed: Q22.3 (E), R94.2
unnamed: Q23.3 (E), R96.2
unnamed: Q24.3 (E), R98.2
unnamed: Q25.3 (E), R100.2
unnamed: Q26.3 (E), R102.2
unnamed: Q27.3 (E), R104.2
unnamed: Q28.3 (E), R106.2
unnamed: Q29.3 (E), R108.2
unnamed: Q30.3 (E), R110.2
unnamed: Q31.3 (E), R112.2
unnamed: Q32.3 (E), R114.2
unnamed: Q33.3 (E), R116.2
unnamed: Q34.3 (E), R118.2
unnamed: Q35.3 (E), R120.2
unnamed: Q36.3 (E), R122.2
unnamed: Q37.3 (E), R124.2
unnamed: Q38.3 (E), R126.2
unnamed: Q39.3 (E), R128.2
unnamed: Q40.3 (E), R130.2
unnamed: Q41.3 (E), R132.2
unnamed: Q42.3 (E), R134.2
unnamed: Q43.3 (E), R136.2
unnamed: Q44.3 (E), R138.2
unnamed: Q45.3 (E), R140.2
unnamed: Q46.3 (E), R142.2
unnamed: Q47.3 (E), R144.2
unnamed: Q48.3 (E), R146.2
unnamed: Q49.3 (E), R148.2
unnamed: Q50.3 (E), R150.2
unnamed: Q51.3 (E), R152.2
unnamed: Q52.3 (E), R154.2
unnamed: Q53.3 (E), R156.2
unnamed: Q54.3 (E), R158.2
unnamed: Q55.3 (E), R160.2
unnamed: Q56.3 (E), R162.2
unnamed: Q57.3 (E), R164.2
unnamed: Q58.3 (E), R166.2
unnamed: Q59.3 (E), R168.2
unnamed: Q60.3 (E), R170.2

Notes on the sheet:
159Hz Low Pass
hFE > 100 Vbe < 0.7
3.3-0.7 / 220 = 11.8mA
Max I: 12mA Avg V: 105V
Theory: if Q fails, resistors will absorb part of the voltage, leaving enough time for the fuse to blow... To be tested!
max W: 140-100 * 0.012 = 0.5W
